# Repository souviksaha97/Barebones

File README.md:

# Barebones
First PCB design, made using Eagle.

Basic barebones Arduino based on the https://learn.sparkfun.com/tutorials/using-eagle-board-layout/all tutorial.

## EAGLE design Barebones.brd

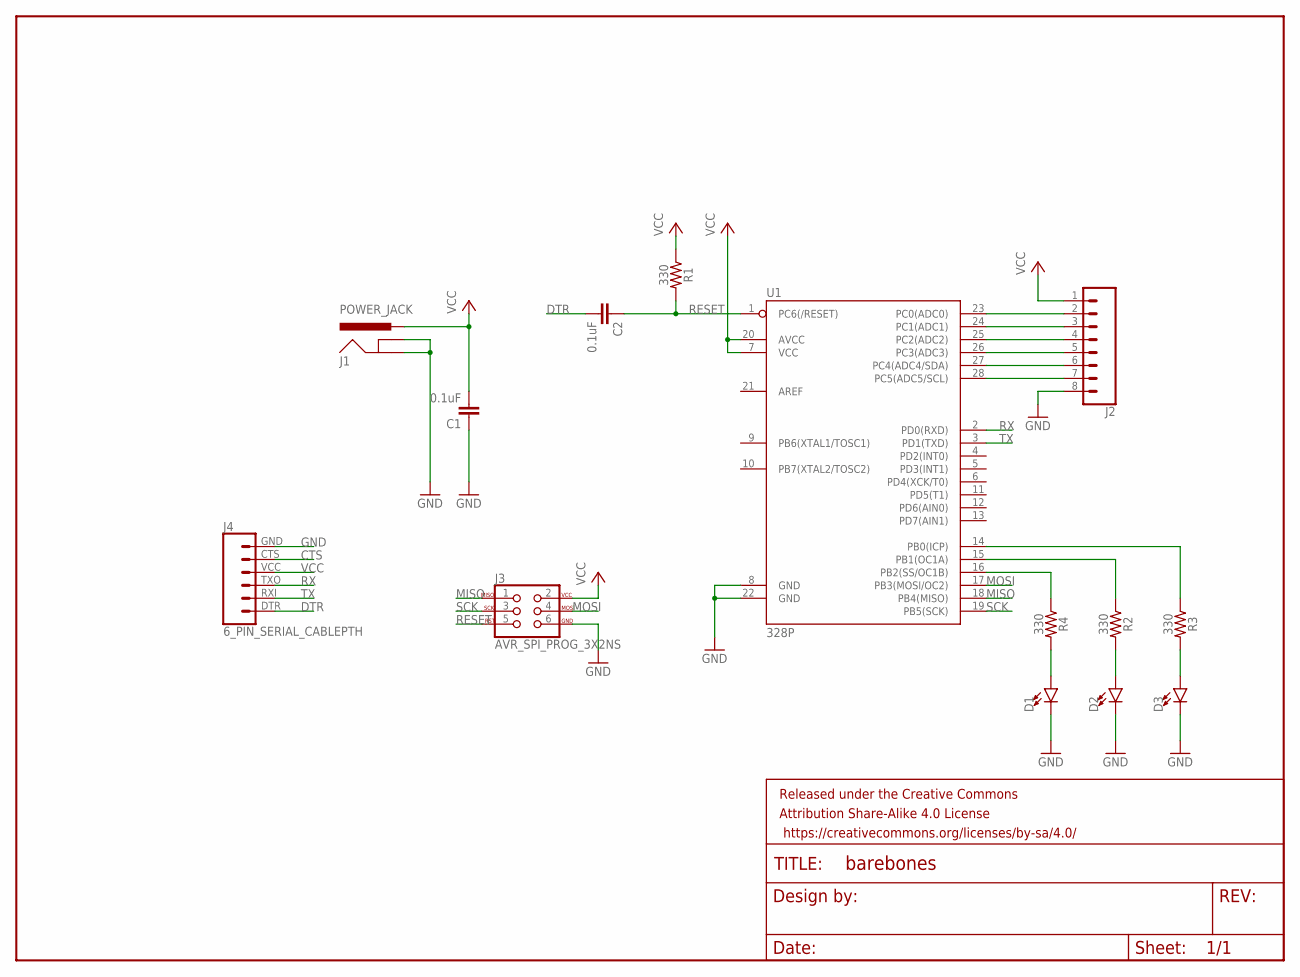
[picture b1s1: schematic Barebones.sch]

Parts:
C1, C2: 0.1uF; CAP-PTH-SMALL-KIT
D1, D2, D3: LED5MM; LED_5MM
FRAME1: FRAME-LETTER; CREATIVE_COMMONS
J1: POWER_JACK; POWER_JACK_PTH
J2: CONN_08"; 1X08
J3: AVR_SPI_PROG_3X2NS; 2X3-NS
J4: 6_PIN_SERIAL_CABLEPTH; FTDI_BASIC
R1, R2, R3, R4: 330; AXIAL-0.3
U1: 328P; DIP28

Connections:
CTS: J4.CTS (5)
DTR: C2.2, J4.DTR (1)
GND: C1.1, D1.K (C), D2.K (C), D3.K (C), J1.GND, J1.GNDBREAK, J2.8, J3.6, J4.GND (6), U1.8 (GND), U1.22 (GND)
MISO: J3.1, U1.18 (PB4(MISO))
MOSI: J3.4, U1.17 (PB3(MOSI/OC2))
unnamed: R3.P$1 (1), U1.14 (PB0(ICP))
unnamed: J2.2, U1.23 (PC0(ADC0))
unnamed: J2.3, U1.24 (PC1(ADC1))
unnamed: J2.4, U1.25 (PC2(ADC2))
unnamed: J2.5, U1.26 (PC3(ADC3))
unnamed: J2.6, U1.27 (PC4(ADC4/SDA))
unnamed: R2.P$1 (1), U1.15 (PB1(OC1A))
unnamed: J2.7, U1.28 (PC5(ADC5/SCL))
unnamed: R4.P$1 (1), U1.16 (PB2(SS/OC1B))
unnamed: D1.A, R4.P$2 (2)
unnamed: D2.A, R2.P$2 (2)
unnamed: D3.A, R3.P$2 (2)
RESET: C2.1, J3.5, R1.P$2 (2), U1.1 (PC6(/RESET))
RX: J4.TXO (3), U1.2 (PD0(RXD))
SCK: J3.3, U1.19 (PB5(SCK))
TX: J4.RXI (2), U1.3 (PD1(TXD))
VCC: C1.2, J1.PWR, J2.1, J3.2, J4.VCC (4), R1.P$1 (1), U1.7 (VCC), U1.20 (AVCC)

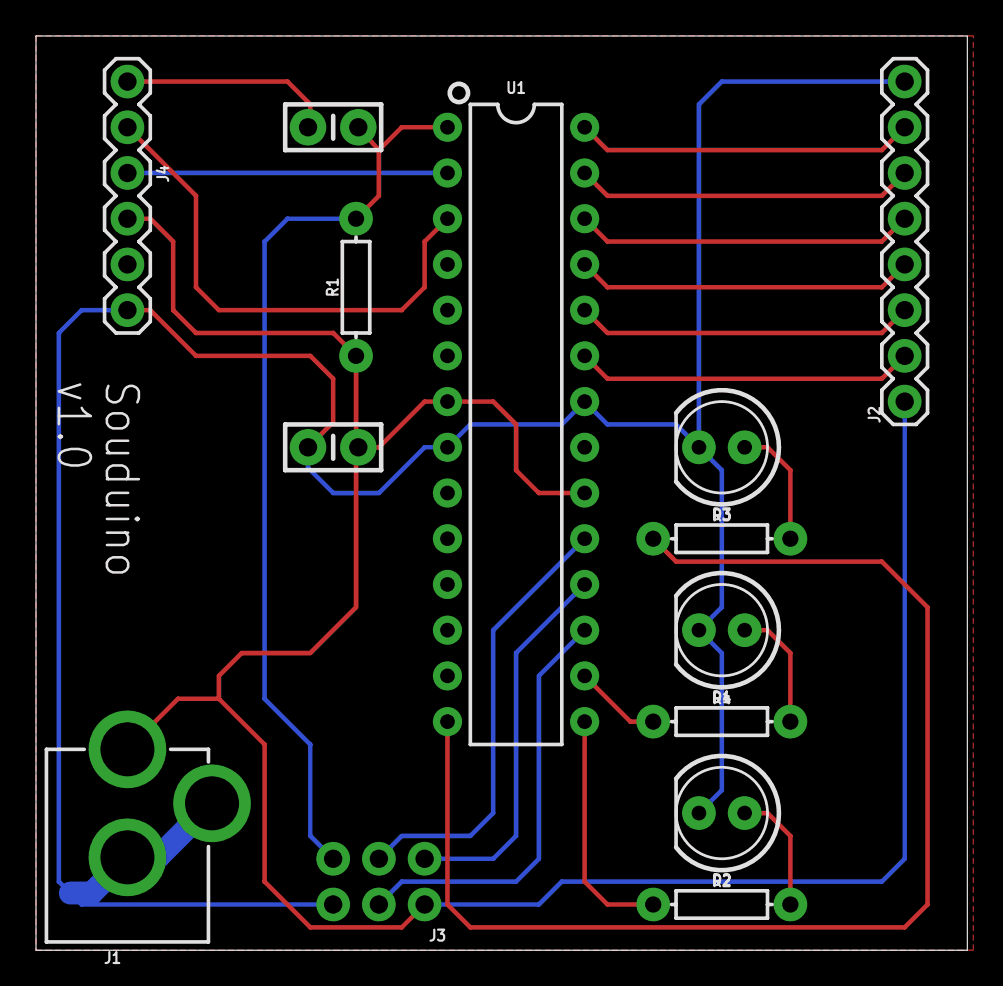
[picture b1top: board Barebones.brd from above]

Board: 2 copper layers, 51.7 x 50.8 mm, 15 parts (0 on the bottom side), 21 nets.

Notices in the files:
parts and their libraries:
SparkFun-Capacitors: Licensing: Creative Commons ShareAlike 4.0 International - https://creativecommons.org/licenses/by-sa/4.0
SparkFun-Aesthetics: Released under the Creative Commons Attribution Share-Alike 4.0 License
SparkFun-Aesthetics: https://creativecommons.org/licenses/by-sa/4.0
